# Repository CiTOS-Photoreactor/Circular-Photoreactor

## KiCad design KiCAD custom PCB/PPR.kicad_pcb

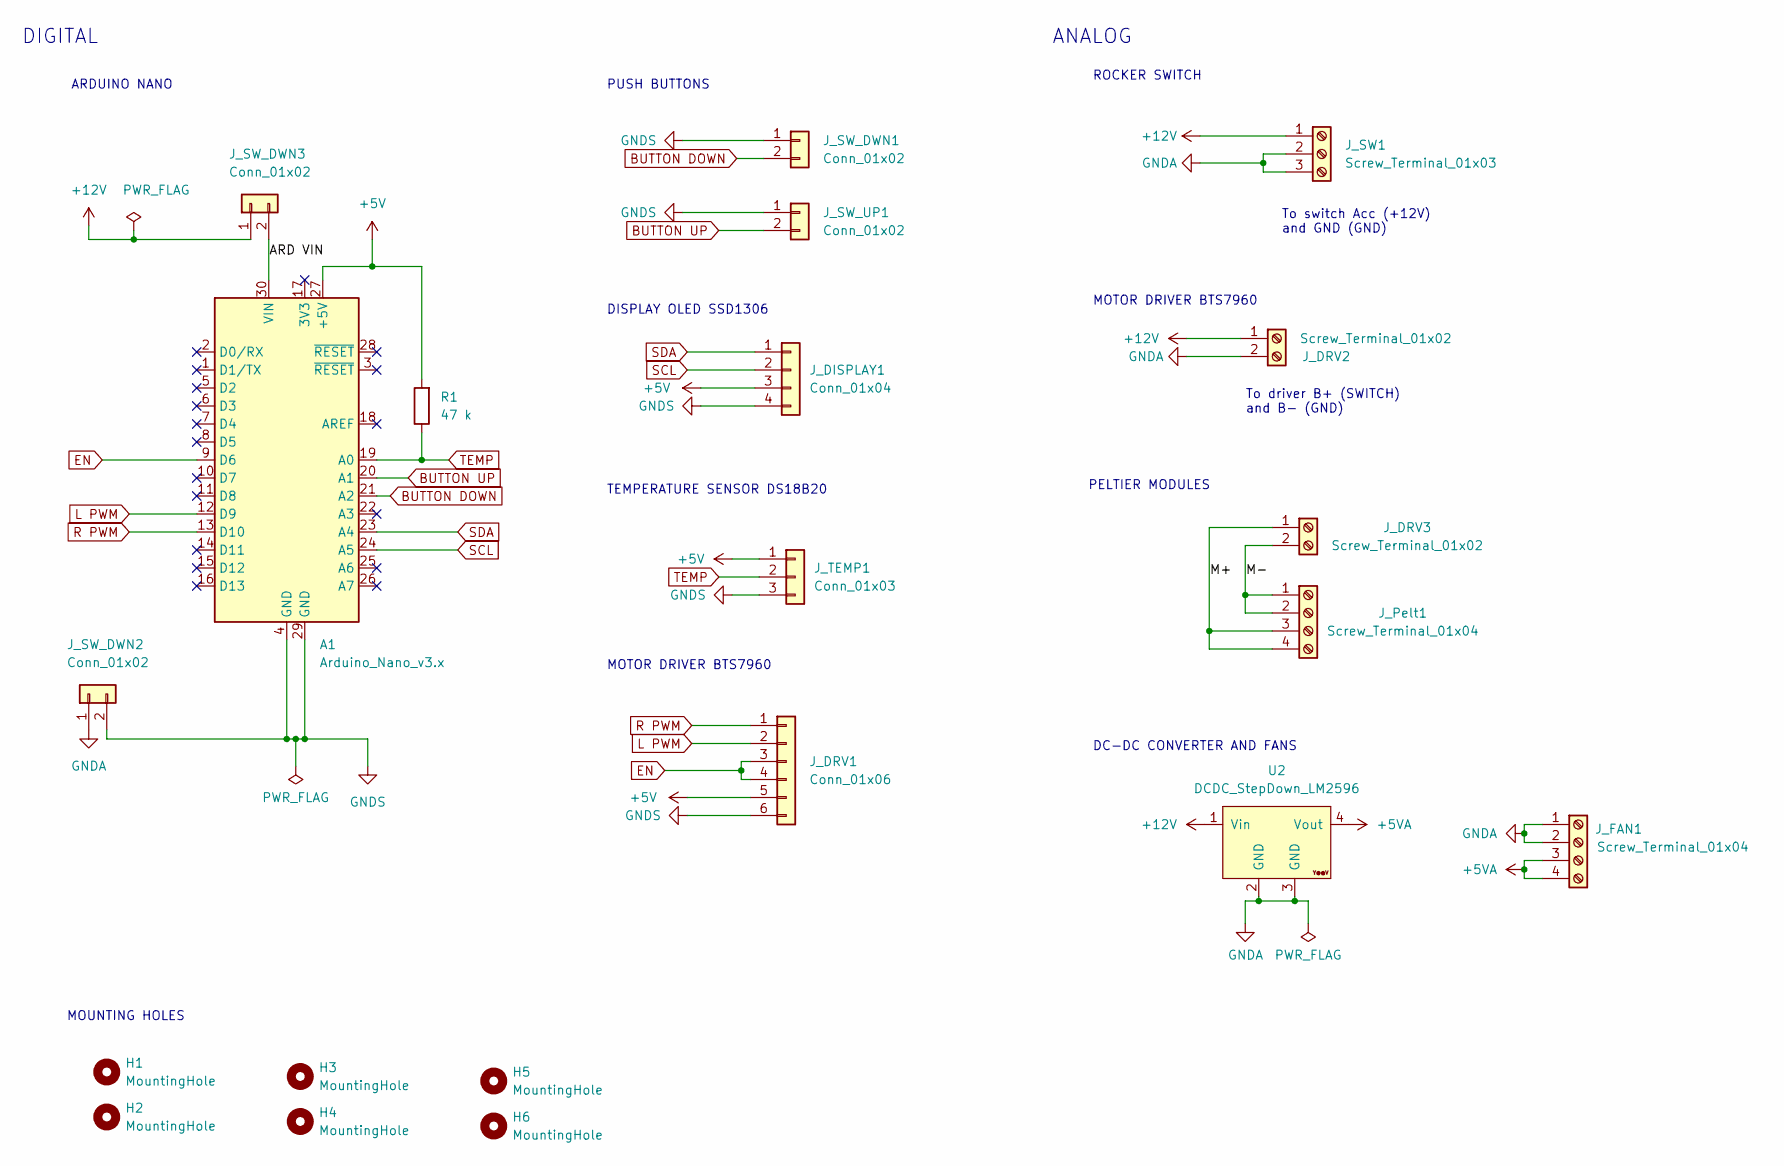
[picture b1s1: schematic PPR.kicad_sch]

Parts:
A1: Arduino_Nano_v3.x; Arduino_Nano
H1, H2, H3, H4: MountingHole; MountingHole_2.2mm_M2
H5, H6: MountingHole; MountingHole_3.2mm_M3
J_DISPLAY1: Conn_01x04; PinHeader_1x04_P2.54mm_Vertical
J_DRV1: Conn_01x06; PinHeader_1x06_P2.54mm_Vertical
J_DRV2, J_DRV3: Screw_Terminal_01x02; TerminalBlock_bornier-2_P5.08mm
J_FAN1: Screw_Terminal_01x04; TerminalBlock_bornier-4_P5.08mm
J_Pelt1: Screw_Terminal_01x04; TerminalBlock_bornier-4_P5.08mm
J_SW1: Screw_Terminal_01x03; TerminalBlock_bornier-3_P5.08mm
J_SW_DWN1, J_SW_DWN2, J_SW_DWN3: Conn_01x02; PinHeader_1x02_P2.54mm_Vertical
J_SW_UP1: Conn_01x02; PinHeader_1x02_P2.54mm_Vertical
J_TEMP1: Conn_01x03; PinHeader_1x03_P2.54mm_Vertical
R1: 47 k; R_Axial_DIN0309_L9.0mm_D3.2mm_P12.70mm_Horizontal
U2: DCDC_StepDown_LM2596; YAAJ_DCDC_StepDown_LM2596

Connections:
+5V: A1.27 (+5V), J_DISPLAY1.3, J_DRV1.5, J_TEMP1.1, R1.2
+5VA: J_FAN1.3, J_FAN1.4, U2.4 (Vout)
+12V: J_DRV2.1, J_SW1.1, J_SW_DWN3.1, U2.1 (Vin)
/ARD VIN: A1.30 (VIN), J_SW_DWN3.2
/M+: J_DRV3.1, J_Pelt1.3, J_Pelt1.4
/M-: J_DRV3.2, J_Pelt1.1, J_Pelt1.2
BUTTON DOWN: A1.21 (A2), J_SW_DWN1.2
BUTTON UP: A1.20 (A1), J_SW_UP1.2
EN: A1.9 (D6), J_DRV1.3, J_DRV1.4
GNDA: J_DRV2.2, J_FAN1.1, J_FAN1.2, J_SW1.2, J_SW1.3, J_SW_DWN2.1, U2.2 (GND), U2.3 (GND)
GNDS: A1.4 (GND), A1.29 (GND), J_DISPLAY1.4, J_DRV1.6, J_SW_DWN1.1, J_SW_DWN2.2, J_SW_UP1.1, J_TEMP1.3
L PWM: A1.12 (D9), J_DRV1.2
R PWM: A1.13 (D10), J_DRV1.1
SCL: A1.24 (A5), J_DISPLAY1.2
SDA: A1.23 (A4), J_DISPLAY1.1
TEMP: A1.19 (A0), J_TEMP1.2, R1.1

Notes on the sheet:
To switch Acc (+12V) and GND (GND)
ROCKER SWITCH
DISPLAY OLED SSD1306
MOUNTING HOLES
TEMPERATURE SENSOR DS18B20
PELTIER MODULES
DIGITAL
ARDUINO NANO
DC-DC CONVERTER AND FANS
PUSH BUTTONS
ANALOG
To driver B+ (SWITCH) and B- (GND)
MOTOR DRIVER BTS7960

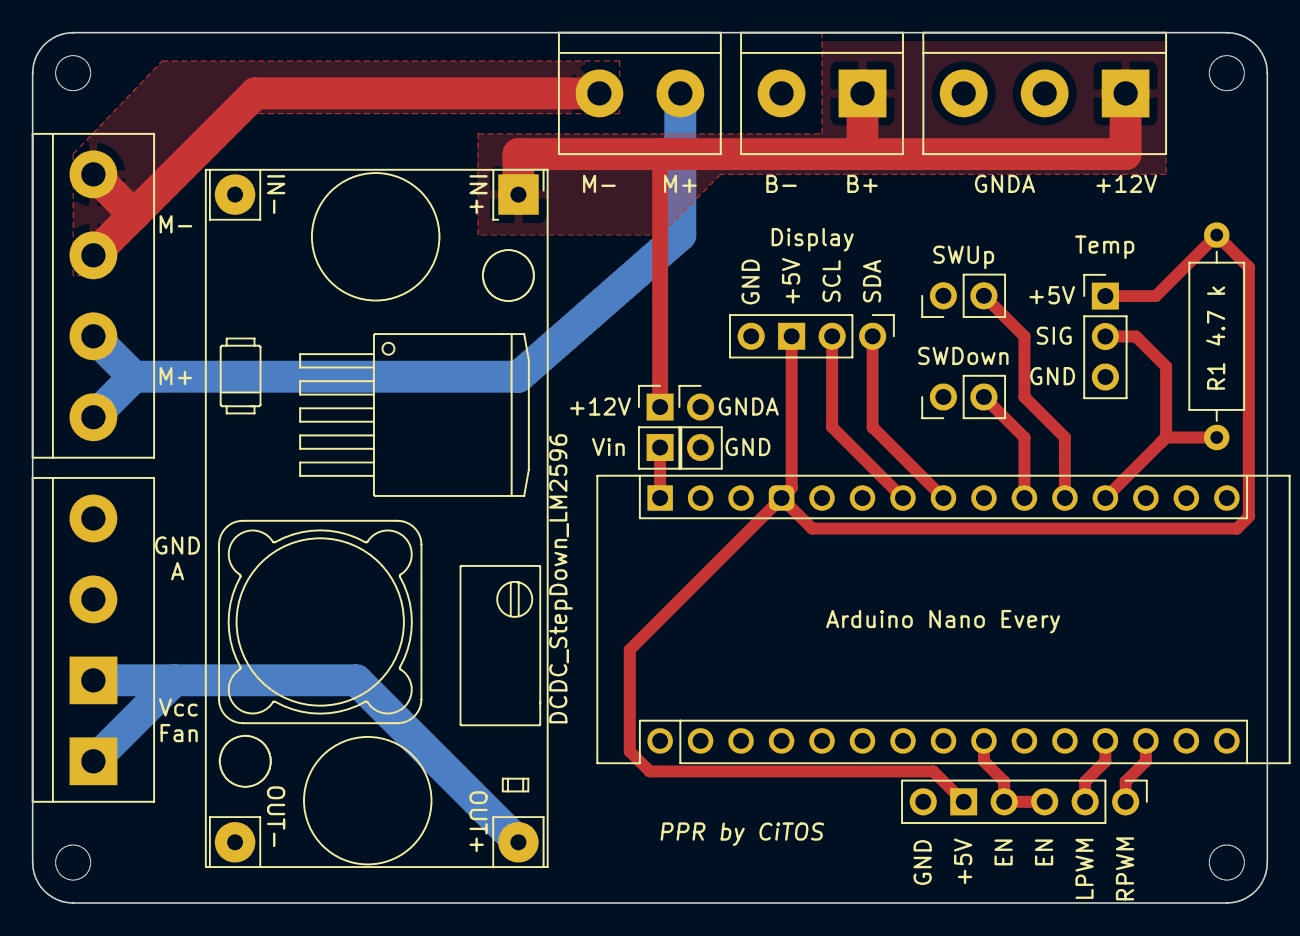
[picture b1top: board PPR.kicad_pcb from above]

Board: 2 copper layers, 77.5 x 54.6 mm, 21 parts (0 on the bottom side), 16 nets.
